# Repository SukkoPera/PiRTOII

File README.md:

# PiRTO II

PiRTO II if a flash multicart for the Mattel Intellivision based on the Raspberry Pico.

## Summary
This is my variation on [Andrea Ottaviani's PiRTO II](https://github.com/aotta/PiRTOII) flash multicart for the Mattel Intellivision.

My original goal was to adapt it in order to use original Pico boards, of which I had plenty. While studying the project I decided to introduce proper level shifting and a MicroSD card slot (since the original Pico has less flash space than the purple clones used in the original project). All of this eventually made the project very similar to Andrea's [first version of the cart](https://github.com/aotta/PiRTO), of which I was unaware of the time, but it uses through-hole components and one less chip.

## Usage
The Pico must be flashed with some firmware. You have a couple of choices:
- If you want to use Andrea's original firmware, you have to use the version from this page, which was changed to reflect the different pin mapping. Do **NOT** use the firmware from the original project, I will try to incorporate any upstream changes. This firmware has **NO SUPPORT** for the SD card slot.
- storm_walker has updated Andrea's firmware to support the SD card slot. You can get his version from [the sd_support branch](https://github.com/SukkoPera/PiRTOII/tree/sd_support). As far as I'm aware, this version **ONLY** supports the SD card slot. Any ROMs stored in the Pico's flash memory will not be usable.
- Alternatively, you can use [the Minty firmware from Gennaro Tortone](https://github.com/gtortone/Minty), which supports this variant starting from version 1.2. This should support both ROMs from the Pico's flash memory and from the SD card.

For any other needs, please refer to [the original project](https://github.com/aotta/PiRTOII) or to the [AtariAge forum](https://forums.atariage.com/forum/125-intellivision-aquarius/).

## Assembly
This board was designed **for the original Raspberry Pico board**, so either use that or a clone that has the same pinout. It's your responsibility to ascertain that.

U2/3/4 **MUST** be 74LVC245. Do **NOT** get these from China, as they will likely be HC chips with just different (incorrect) markings. Rather get them from Mouser, Digikey, RS, etc.

Other BJTs will probably work for Q1, just make sure they have the same pinout.

JP1/2/3/4 are experimental jumpers and all of them **except** JP4 **MUST** be closed for the moment.

## Releases
If you want to get this board produced, you are recommended to get [the latest release](https://github.com/SukkoPera/PiRTOII/releases) rather than the current git version, as the latter might be under development and is not guaranteed to be working.

Every release is accompanied by its Bill Of Materials (BOM) file and any relevant notes about it, which you are recommended to read carefully.

## License
Despite [an effort to clear things up](https://github.com/aotta/PiRTOII/issues/2), the license status of Andrea's original board is unclear, so I don't really know what to do. I don't want to add or remove any limitations compared to the original project, so please get in touch with him before you use this project in any way.

Still, let me point out that this PiRTOII variation is provided to you ‘as is’ and without any express or implied warranties whatsoever with respect to its functionality, operability or use, including, without limitation, any implied warranties of merchantability, fitness for a particular purpose or infringement. We expressly disclaim any liability whatsoever for any direct, indirect, consequential, incidental or special damages, including, without limitation, lost revenues, lost profits, losses resulting from business interruption or loss of data, regardless of the form of action or legal theory under which the liability may be asserted, even if advised of the possibility or likelihood of such damages.

## Support the Project
If you want to get some boards manufactured, you can get them from PCBWay through this link:

You get my gratitude and cheap, professionally-made and good quality PCBs, I get some credit that will help with this and [other projects](https://www.pcbway.com/project/member/?bmbno=72D33927-5EF6-42). You won't even have to worry about the various PCB options, it's all pre-configured for you!

Also, if you still have to register, [you can use this link](https://pcbway.com/g/Nz7XZs) to get some bonus initial credit (and yield me some more).

You can also buy me a coffee if you want, all the money collected this way will actually go to charity:

## Thanks
Of course, I would like to thank Andrea for his original project.

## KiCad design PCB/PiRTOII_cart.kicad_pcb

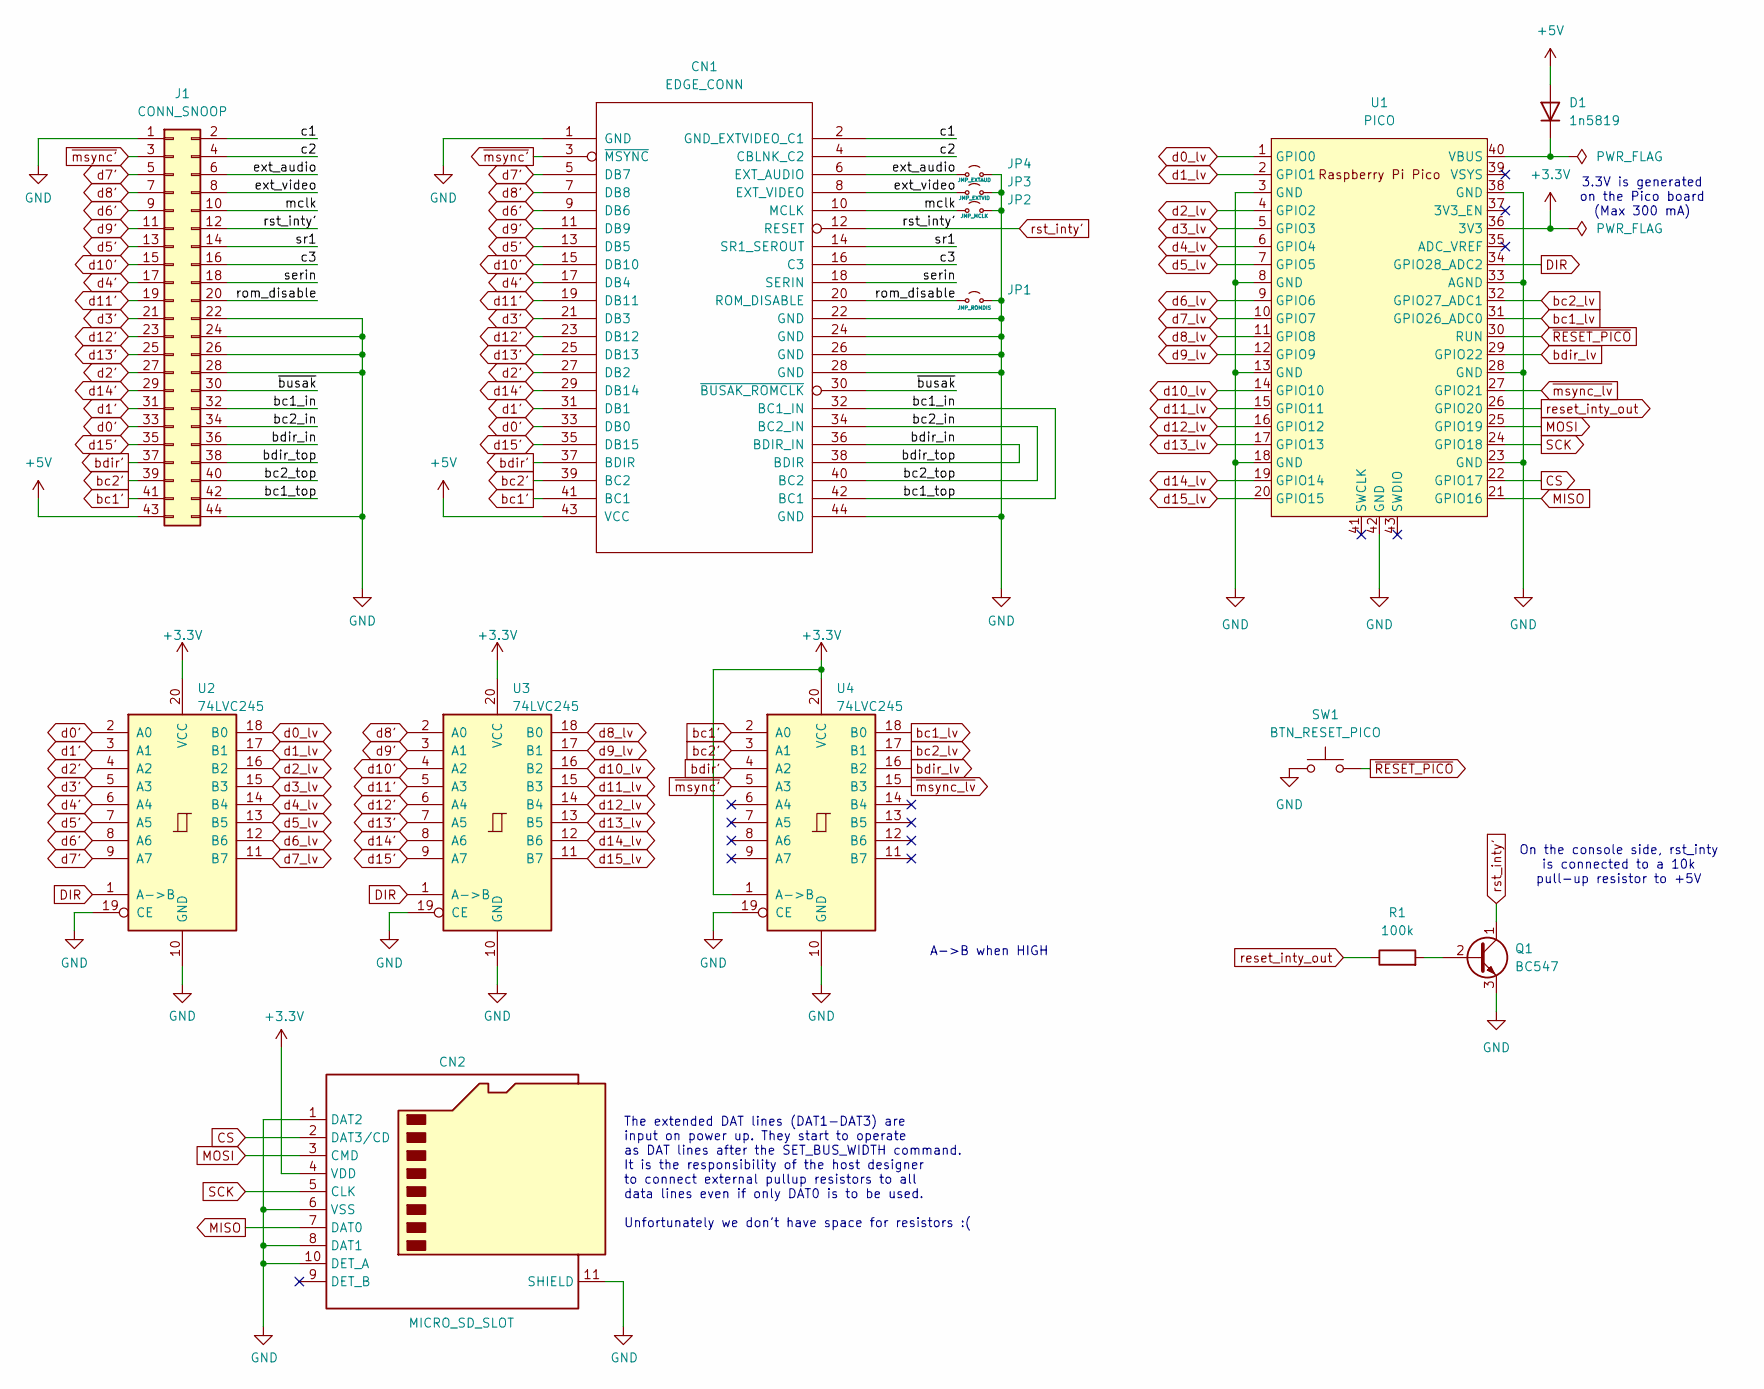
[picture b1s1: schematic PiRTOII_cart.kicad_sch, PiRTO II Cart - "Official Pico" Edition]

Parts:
CN1: EDGE_CONN; Intellivision_Edge_Connector
CN2: MICRO_SD_SLOT; GCT-MEM2055-00-190-01-A
D1: 1n5819; D_DO-41_SOD81_P10.16mm_Horizontal
J1: CONN_SNOOP; PinHeader_2x22_P2.54mm_Vertical
JP1: JMP_ROMDIS; SolderJumper-2_P1.3mm_Open_RoundedPad1.0x1.5mm
JP2: JMP_MCLK; SolderJumper-2_P1.3mm_Open_RoundedPad1.0x1.5mm
JP3: JMP_EXTVID; SolderJumper-2_P1.3mm_Open_RoundedPad1.0x1.5mm
JP4: JMP_EXTAUD; SolderJumper-2_P1.3mm_Open_RoundedPad1.0x1.5mm
Q1: BC547; TO-92_HandSolder
R1: 100k; R_Axial_DIN0207_L6.3mm_D2.5mm_P10.16mm_Horizontal
SW1: BTN_RESET_PICO; SW_Tactile_SPST_Angled_PTS645Vx83-2LFS
U1: PICO; RPi_Pico_SMD_TH
U2, U3, U4: 74LVC245; DIP-20_W7.62mm_Socket_LongPads

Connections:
+3.3V: CN2.4 (VDD), U1.36 (3V3), U2.20 (VCC), U3.20 (VCC), U4.1 (A->B), U4.20 (VCC)
+5V: CN1.43 (VCC), D1.2 (A), J1.43
/bc1_in: CN1.32 (BC1_IN), CN1.42 (BC1), J1.32, J1.42
/bc2_in: CN1.34 (BC2_IN), CN1.40 (BC2), J1.34, J1.40
/bdir_in: CN1.36 (BDIR_IN), CN1.38 (BDIR), J1.36, J1.38
/c1: CN1.2 (GND_EXTVIDEO_C1), J1.2
/c2: CN1.4 (CBLNK_C2), J1.4
/c3: CN1.16 (C3), J1.16
/ext_audio: CN1.6 (EXT_AUDIO), J1.6, JP4.1 (A)
/ext_video: CN1.8 (EXT_VIDEO), J1.8, JP3.1 (A)
/mclk: CN1.10 (MCLK), J1.10, JP2.1 (A)
/rom_disable: CN1.20 (ROM_DISABLE), J1.20, JP1.1 (A)
/serin: CN1.18 (SERIN), J1.18
/sr1: CN1.14 (SR1_SEROUT), J1.14
/~busak: CN1.30 (~BUSAK_ROMCLK), J1.30
CS: CN2.2 (DAT3/CD), U1.22 (GPIO17)
DIR: U1.34 (GPIO28_ADC2), U2.1 (A->B), U3.1 (A->B)
GND: CN1.1 (GND), CN1.22 (GND), CN1.24 (GND), CN1.26 (GND), CN1.28 (GND), CN1.44 (GND), CN2.1 (DAT2), CN2.6 (VSS), CN2.8 (DAT1), CN2.10 (DET_A), CN2.11 (SHIELD), J1.1, J1.22, J1.24, J1.26, J1.28, J1.44, JP1.2 (B), JP2.2 (B), JP3.2 (B), JP4.2 (B), Q1.3 (E), SW1.1, U1.3 (GND), U1.8 (GND), U1.13 (GND), U1.18 (GND), U1.23 (GND), U1.28 (GND), U1.33 (AGND), U1.38 (GND), U1.42 (GND), U2.10 (GND), U2.19 (CE), U3.10 (GND), U3.19 (CE), U4.10 (GND), U4.19 (CE)
MISO: CN2.7 (DAT0), U1.21 (GPIO16)
MOSI: CN2.3 (CMD), U1.25 (GPIO19)
unnamed: D1.1 (K), U1.40 (VBUS)
unnamed: Q1.2 (B), R1.2
SCK: CN2.5 (CLK), U1.24 (GPIO18)
bc1': CN1.41 (BC1), J1.41, U4.2 (A0)
bc1_lv: U1.31 (GPIO26_ADC0), U4.18 (B0)
bc2': CN1.39 (BC2), J1.39, U4.3 (A1)
bc2_lv: U1.32 (GPIO27_ADC1), U4.17 (B1)
bdir': CN1.37 (BDIR), J1.37, U4.4 (A2)
bdir_lv: U1.29 (GPIO22), U4.16 (B2)
d0': CN1.33 (DB0), J1.33, U2.2 (A0)
d0_lv: U1.1 (GPIO0), U2.18 (B0)
d1': CN1.31 (DB1), J1.31, U2.3 (A1)
d1_lv: U1.2 (GPIO1), U2.17 (B1)
d2': CN1.27 (DB2), J1.27, U2.4 (A2)
d2_lv: U1.4 (GPIO2), U2.16 (B2)
d3': CN1.21 (DB3), J1.21, U2.5 (A3)
d3_lv: U1.5 (GPIO3), U2.15 (B3)
d4': CN1.17 (DB4), J1.17, U2.6 (A4)
d4_lv: U1.6 (GPIO4), U2.14 (B4)
d5': CN1.13 (DB5), J1.13, U2.7 (A5)
d5_lv: U1.7 (GPIO5), U2.13 (B5)
d6': CN1.9 (DB6), J1.9, U2.8 (A6)
d6_lv: U1.9 (GPIO6), U2.12 (B6)
d7': CN1.5 (DB7), J1.5, U2.9 (A7)
d7_lv: U1.10 (GPIO7), U2.11 (B7)
d8': CN1.7 (DB8), J1.7, U3.2 (A0)
d8_lv: U1.11 (GPIO8), U3.18 (B0)
d9': CN1.11 (DB9), J1.11, U3.3 (A1)
d9_lv: U1.12 (GPIO9), U3.17 (B1)
d10': CN1.15 (DB10), J1.15, U3.4 (A2)
d10_lv: U1.14 (GPIO10), U3.16 (B2)
d11': CN1.19 (DB11), J1.19, U3.5 (A3)
d11_lv: U1.15 (GPIO11), U3.15 (B3)
d12': CN1.23 (DB12), J1.23, U3.6 (A4)
d12_lv: U1.16 (GPIO12), U3.14 (B4)
d13': CN1.25 (DB13), J1.25, U3.7 (A5)
d13_lv: U1.17 (GPIO13), U3.13 (B5)
d14': CN1.29 (DB14), J1.29, U3.8 (A6)
d14_lv: U1.19 (GPIO14), U3.12 (B6)
d15': CN1.35 (DB15), J1.35, U3.9 (A7)
d15_lv: U1.20 (GPIO15), U3.11 (B7)
reset_inty_out: R1.1, U1.26 (GPIO20)
rst_inty': CN1.12 (RESET), J1.12, Q1.1 (C)
~RESET_PICO: SW1.2, U1.30 (RUN)
~msync': CN1.3 (~MSYNC), J1.3, U4.5 (A3)
~msync_lv: U1.27 (GPIO21), U4.15 (B3)

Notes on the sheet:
A->B when HIGH
3.3V is generated on the Pico board (Max 300 mA)
On the console side, rst_inty is connected to a 10k pull-up resistor to +5V
The extended DAT lines (DAT1-DAT3) are input on power up. They start to operate as DAT lines after the SET_BUS_WIDTH command. It is the responsibility of the host designer to connect external pullup resistors to all data lines even if only DAT0 is to be used. Unfortunately we don't have space for r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

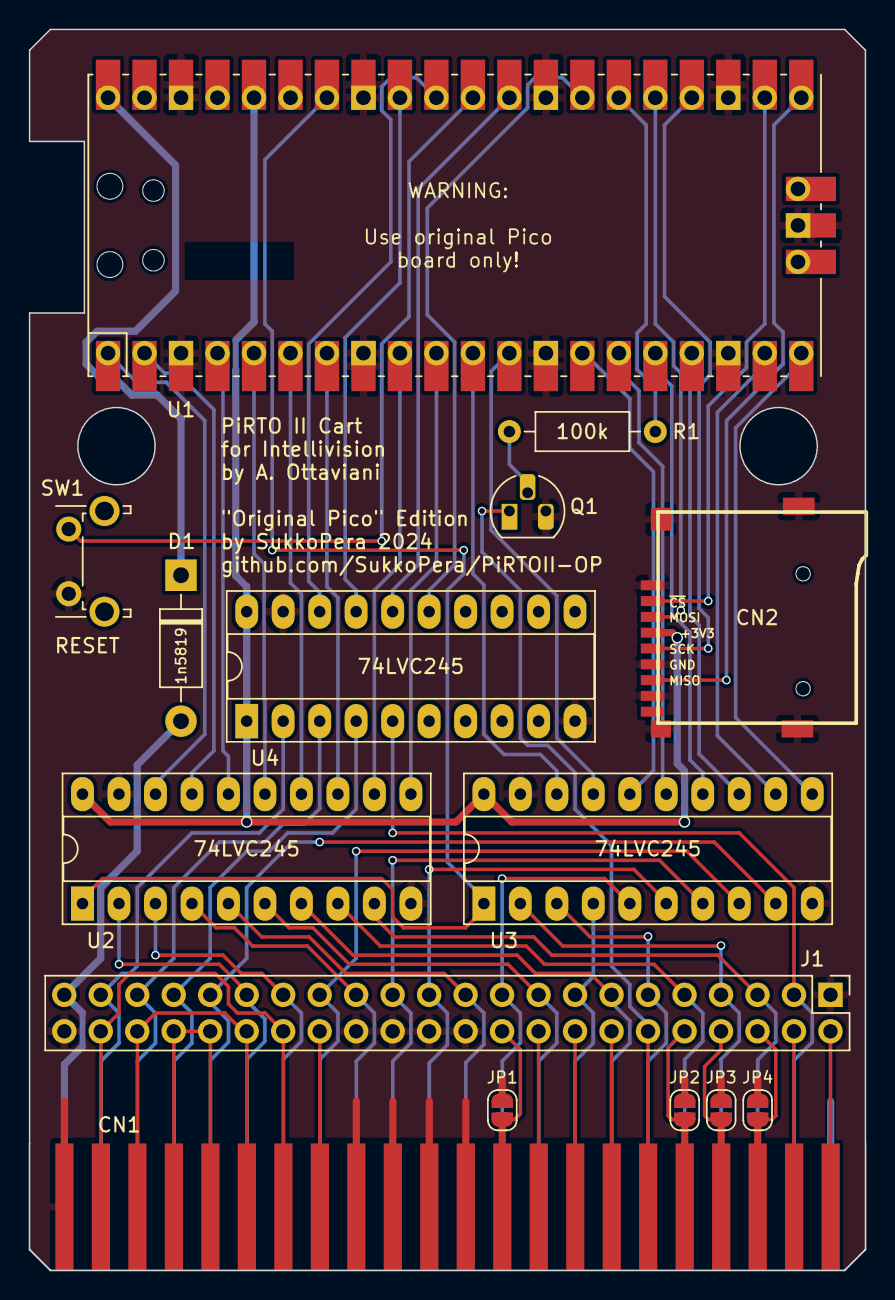
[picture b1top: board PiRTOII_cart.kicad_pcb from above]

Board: 2 copper layers, 58.2 x 86.4 mm, 15 parts (0 on the bottom side), 66 nets.

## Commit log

2024-12-05 Use better BJT footprint
2024-12-05 Add MicroSD slot
2024-12-05 Use original Pico board
2024-12-05 Add SD slot signal labels (?)
2024-12-05 Almost there
2024-12-05 Adapt code to original Pico board
2024-12-22 Remove files that can be found upstream
2024-12-22 Add renders
2024-12-22 Rename renders
2024-12-28 Use the two BC1/2/BDIR sets more properly
2025-02-03 Add SD support - Thanks storm_walker!
2025-02-03 Add missing SPI driver
2025-02-03 Restore Windows-style EOLs in IntyBasic files
2025-04-12 Fix max number of dir entries
    (cherry picked from upstream commit bd78ca32517b8900df6ca5afb25b20ff275c1429)
2025-04-12 asm inline -> asm volatile
2025-04-12 Remove leftover myboard.h
2025-04-12 FatFs_SPI -> FatFS_SPI
2026-02-13 Add badges and update donation link in README
    Added GitHub badges for release information and updated the coffee donation link image.
